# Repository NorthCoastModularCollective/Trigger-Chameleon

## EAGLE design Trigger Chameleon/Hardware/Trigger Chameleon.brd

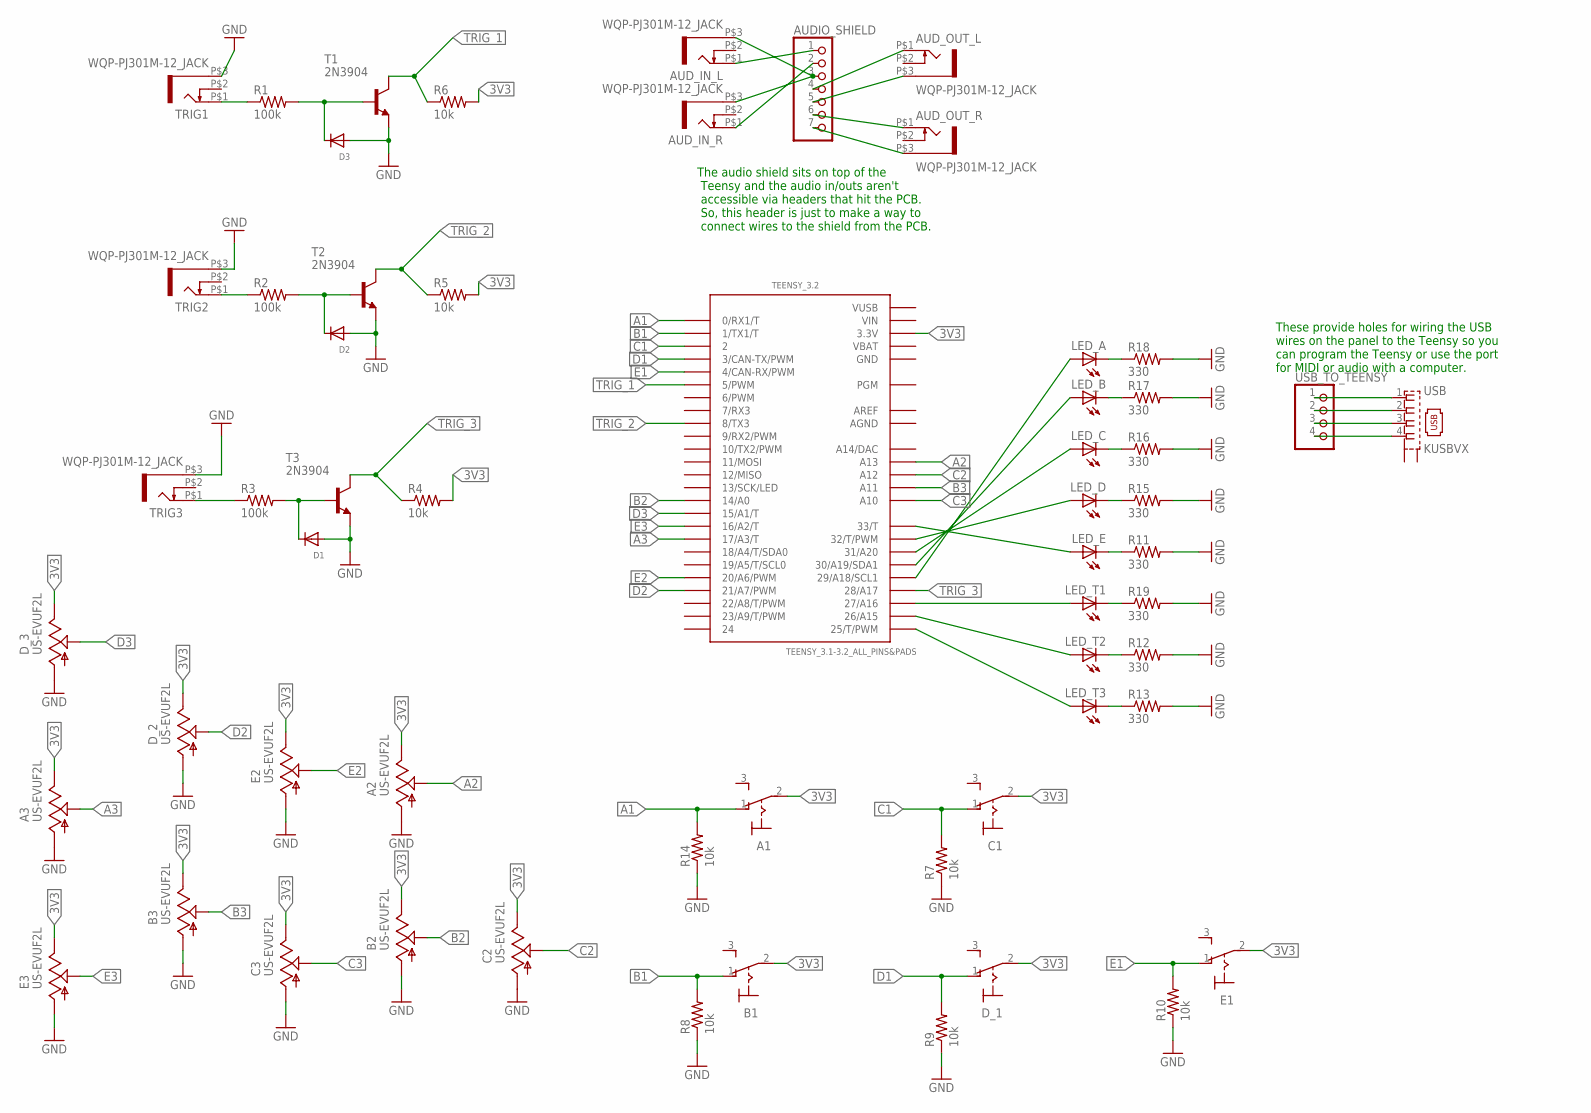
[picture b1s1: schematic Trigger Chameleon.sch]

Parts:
A1: M9040P
A2, A3: US-EVUF2L; EVUFXL
AUDIO_SHIELD: PINHD-1X7; 1X07
AUD_IN_L: WQP-PJ301M-12_JACK
AUD_IN_R: WQP-PJ301M-12_JACK
AUD_OUT_L: WQP-PJ301M-12_JACK
AUD_OUT_R: WQP-PJ301M-12_JACK
B1: M9040P
B2, B3: US-EVUF2L; EVUFXL
C1: M9040P
C2, C3: US-EVUF2L; EVUFXL
D1, D2, D3: DIODESOD-123; SOD-123
D_1: M9040P
D_2, D_3: US-EVUF2L; EVUFXL
E1: M9040P
E2, E3: US-EVUF2L; EVUFXL
LED_A: LED3MM
LED_B: LED3MM
LED_C: LED3MM
LED_D: LED3MM
LED_E: LED3MM
LED_T1, LED_T2, LED_T3: LED3MM
R1, R2, R3: 100k; R0805
R4, R5, R6, R7, R8, R9, R10, R14: 10k; R0805
R11, R12, R13, R15, R16, R17, R18, R19: 330; R0805
T1, T2, T3: 2N3904; TO92
TEENSY_3.2: TEENSY_3.1-3.2_ALL_PINS&PADS; TEENSY_3.0-3.2_ALL_PINS_&_PADS
TRIG1, TRIG2, TRIG3: WQP-PJ301M-12_JACK
USB: KUSBVX
USB_TO_TEENSY: PINHD-1X4; 1X04

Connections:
3V3: A1.2, A2.3 (E), A3.3 (E), B1.2, B2.3 (E), B3.3 (E), C1.2, C2.3 (E), C3.3 (E), D_1.2, D_2.3 (E), D_3.3 (E), E1.2, E2.3 (E), E3.3 (E), R4.2, R5.2, R6.2, TEENSY_3.2.3.3V, TEENSY_3.2.3.3V1 (3.3V), TEENSY_3.2.3.3V2 (3.3V)
A1: A1.1 (O), R14.2, TEENSY_3.2.0 (0/RX1/T)
A2: A2.2 (S), TEENSY_3.2.A13
A3: A3.2 (S), TEENSY_3.2.17/A3 (17/A3/T)
AGND: TEENSY_3.2.AGND
AREF: TEENSY_3.2.AREF
B1: B1.1 (O), R8.2, TEENSY_3.2.1 (1/TX1/T)
B2: B2.2 (S), TEENSY_3.2.14/A0
B3: B3.2 (S), TEENSY_3.2.A11
C1: C1.1 (O), R7.2, TEENSY_3.2.2
C2: C2.2 (S), TEENSY_3.2.A12
C3: C3.2 (S), TEENSY_3.2.A10
D1: D_1.1 (O), R9.2, TEENSY_3.2.3 (3/CAN-TX/PWM)
D2: D_2.2 (S), TEENSY_3.2.21/A7 (21/A7/PWM)
D3: D_3.2 (S), TEENSY_3.2.15/A1 (15/A1/T)
E1: E1.1 (O), R10.2, TEENSY_3.2.4 (4/CAN-RX/PWM)
E2: E2.2 (S), TEENSY_3.2.20/A6 (20/A6/PWM)
E3: E3.2 (S), TEENSY_3.2.16/A2 (16/A2/T)
GND: A2.1 (A), A3.1 (A), B2.1 (A), B3.1 (A), C2.1 (A), C3.1 (A), D1.A, D2.A, D3.A, D_2.1 (A), D_3.1 (A), E3.1 (A), R7.1, R8.1, R9.1, R10.1, R11.2, R12.2, R13.2, R14.1, R15.2, R16.2, R17.2, R18.2, R19.2, T1.3 (E), T2.3 (E), T3.3 (E), TEENSY_3.2.GND, TEENSY_3.2.GND1 (GND), TEENSY_3.2.GND2 (GND), TRIG1.P$3 (1), TRIG2.P$3 (1), TRIG3.P$3 (1)
unnamed: R3.1, TRIG3.P$1 (2)
unnamed: R2.1, TRIG2.P$1 (2)
unnamed: R1.1, TRIG1.P$1 (2)
unnamed: D3.C, R1.2, T1.2 (B)
unnamed: D2.C, R2.2, T2.2 (B)
unnamed: D1.C, R3.2, T3.2 (B)
unnamed: LED_D.K (C), R15.1
unnamed: LED_C.K (C), R16.1
unnamed: LED_B.K (C), R17.1
unnamed: LED_A.K (C), R18.1
unnamed: LED_E.K (C), R11.1
unnamed: LED_T3.K (C), R13.1
unnamed: LED_T2.K (C), R12.1
unnamed: AUDIO_SHIELD.1, AUD_IN_L.P$1 (2)
unnamed: AUDIO_SHIELD.2, AUD_IN_R.P$1 (2)
unnamed: AUDIO_SHIELD.6, AUD_OUT_R.P$1 (2)
unnamed: AUDIO_SHIELD.4, AUD_OUT_L.P$1 (2)
unnamed: LED_T1.K (C), R19.1
unnamed: LED_A.A, TEENSY_3.2.29 (29/A18/SCL1)
unnamed: LED_B.A, TEENSY_3.2.30 (30/A19/SDA1)
unnamed: LED_C.A, TEENSY_3.2.31 (31/A20)
unnamed: LED_D.A, TEENSY_3.2.32 (32/T/PWM)
unnamed: LED_E.A, TEENSY_3.2.33 (33/T)
unnamed: AUDIO_SHIELD.7, AUD_OUT_R.P$3 (1)
unnamed: AUDIO_SHIELD.5, AUD_OUT_L.P$3 (1)
unnamed: AUDIO_SHIELD.3, AUD_IN_L.P$3 (1), AUD_IN_R.P$3 (1)
unnamed: LED_T1.A, TEENSY_3.2.27 (27/A16)
unnamed: LED_T2.A, TEENSY_3.2.26 (26/A15)
unnamed: LED_T3.A, TEENSY_3.2.25 (25/T/PWM)
unnamed: USB.1, USB_TO_TEENSY.1
unnamed: USB.2, USB_TO_TEENSY.2
unnamed: USB.3, USB_TO_TEENSY.3
unnamed: USB.4, USB_TO_TEENSY.4
TRIG_1: R6.1, T1.1 (C), TEENSY_3.2.5 (5/PWM)
TRIG_2: R5.1, T2.1 (C), TEENSY_3.2.8 (8/TX3)
TRIG_3: R4.1, T3.1 (C), TEENSY_3.2.28 (28/A17)
VBAT: TEENSY_3.2.VBAT
VIN: TEENSY_3.2.VIN
VUSB: TEENSY_3.2.VUSB

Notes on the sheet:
The audio shield sits on top of the Teensy and the audio in/outs aren't accessible via headers that hit the PCB. So, this header is just to make a way to connect wires to the shield from the PCB.
These provide holes for wiring the USB wires on the panel to the Teensy so you can program the Teensy or use the port for MIDI or audio with a computer.

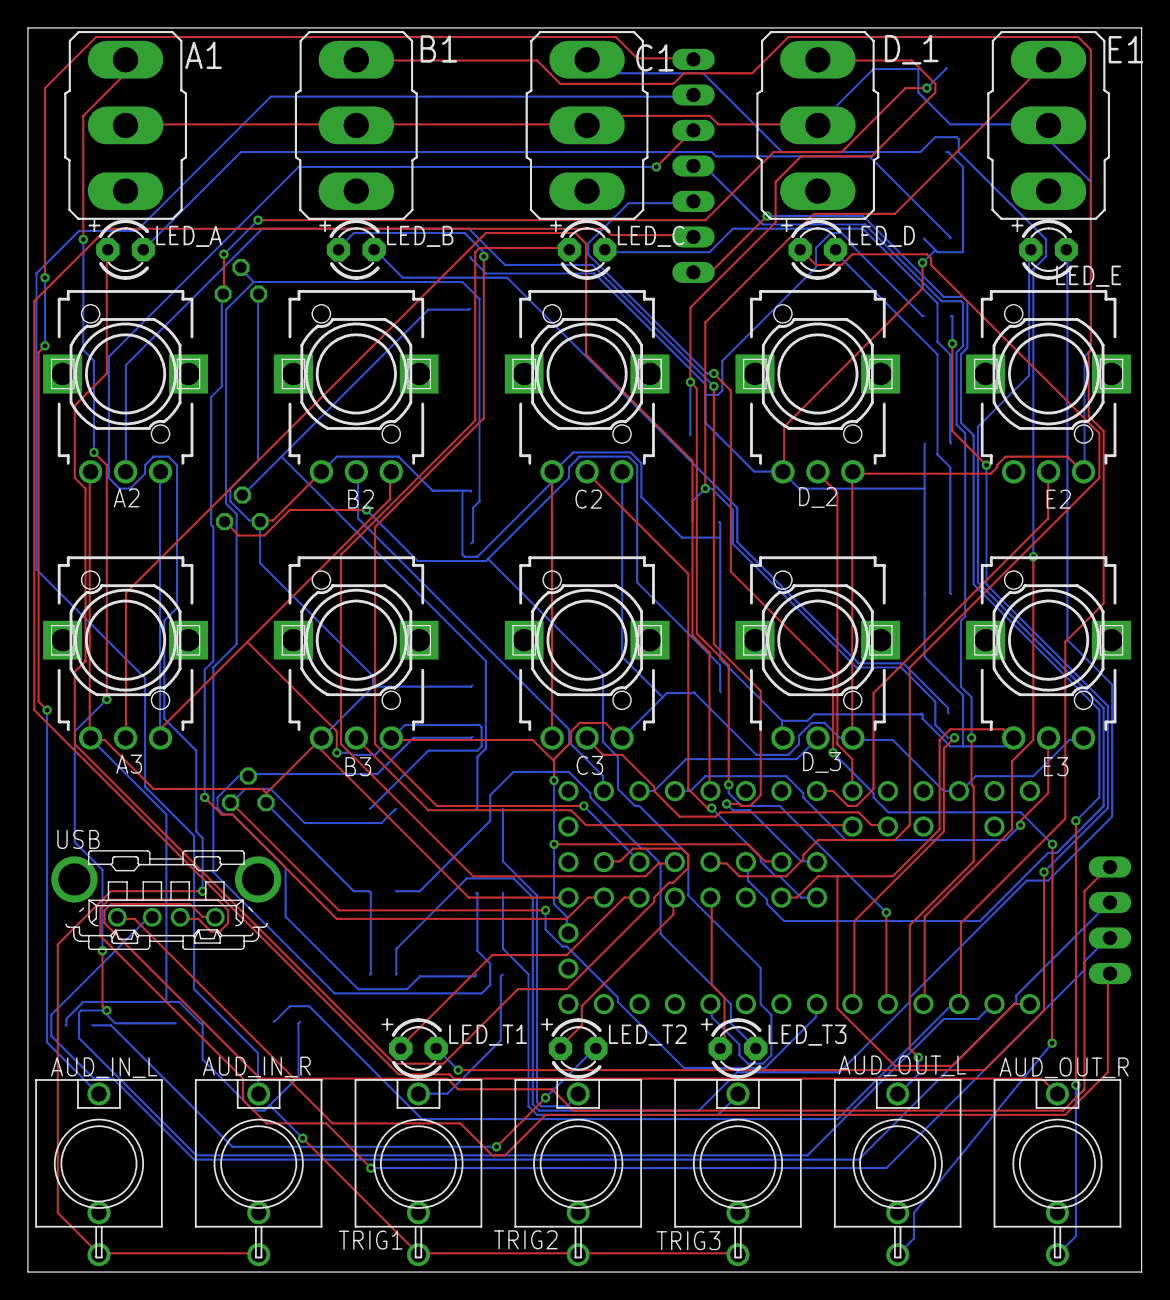
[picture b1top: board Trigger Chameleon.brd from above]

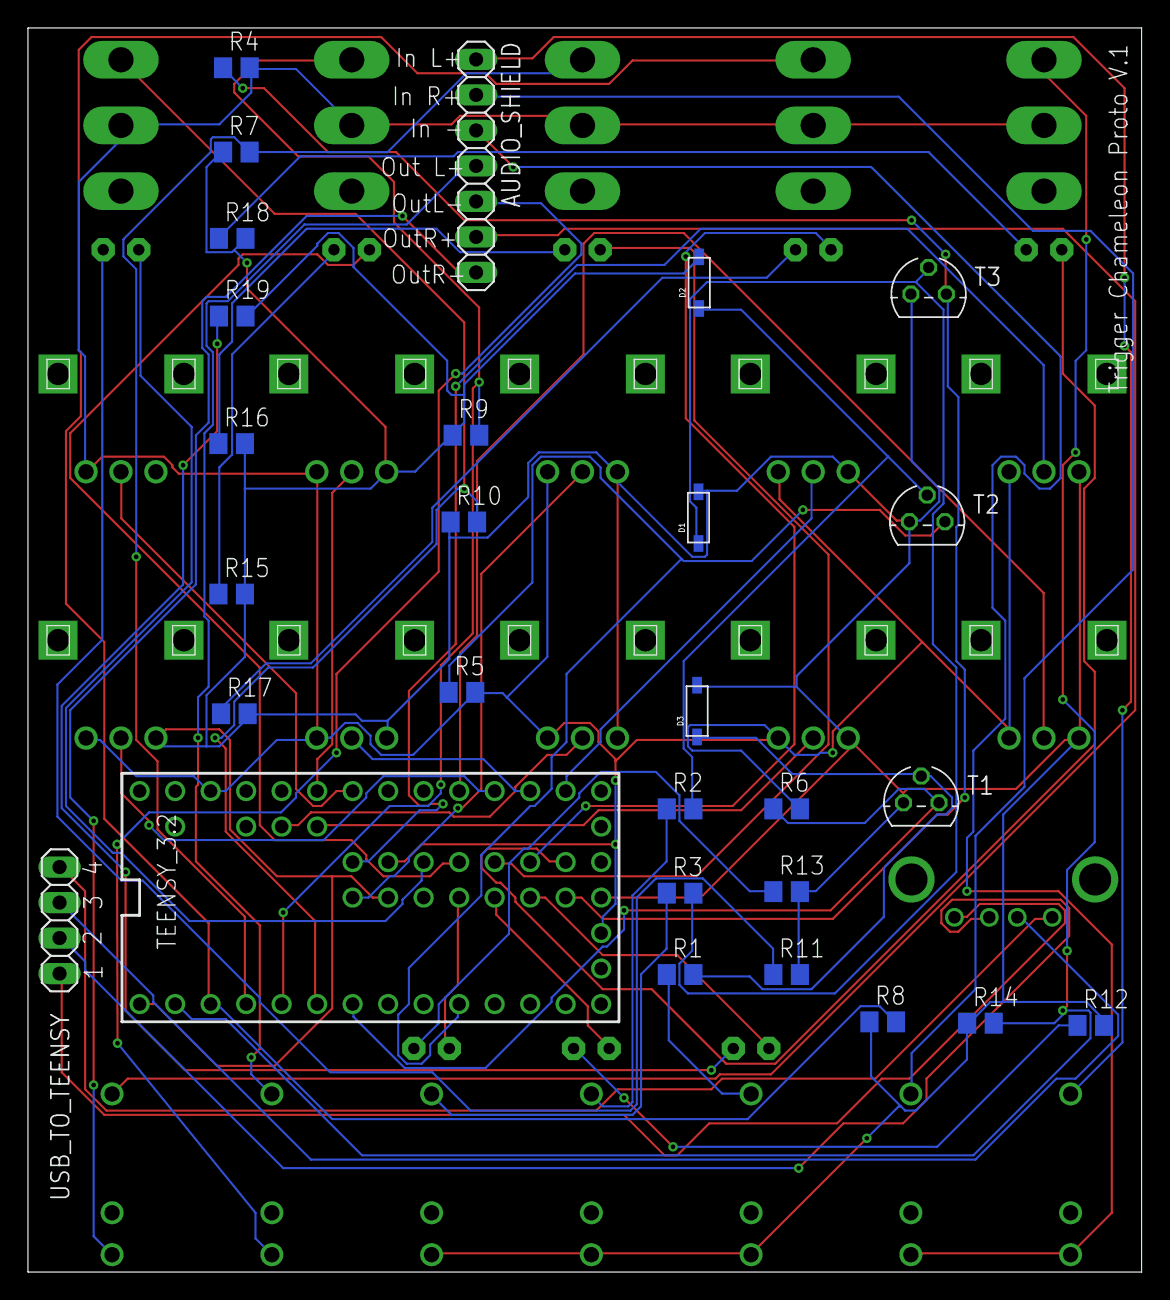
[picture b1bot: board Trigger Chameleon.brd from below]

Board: 2 copper layers, 79.7 x 89.0 mm, 59 parts (28 on the bottom side), 53 nets.

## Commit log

2017-05-22 Update LICENSE
2017-05-23 First upload of current materials
    These materials are still under development. There are incomplete parts, gaps, and bugs galore.
2017-05-24 Panel Eagle File
2017-05-24 Initial upload of current files
2017-06-23 First full version of code
    This code turns Trigger Chameleon into a two voice drum module. Each row of knobs controls one drum voice. It has pitch, shape (envelope), modulation ("colder" and "warmer"), bit reduction, and sampl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
2017-06-23 There's a new version now
2017-06-23 Set theme jekyll-theme-architect
2017-12-13 fixed bug with trigger inputs
